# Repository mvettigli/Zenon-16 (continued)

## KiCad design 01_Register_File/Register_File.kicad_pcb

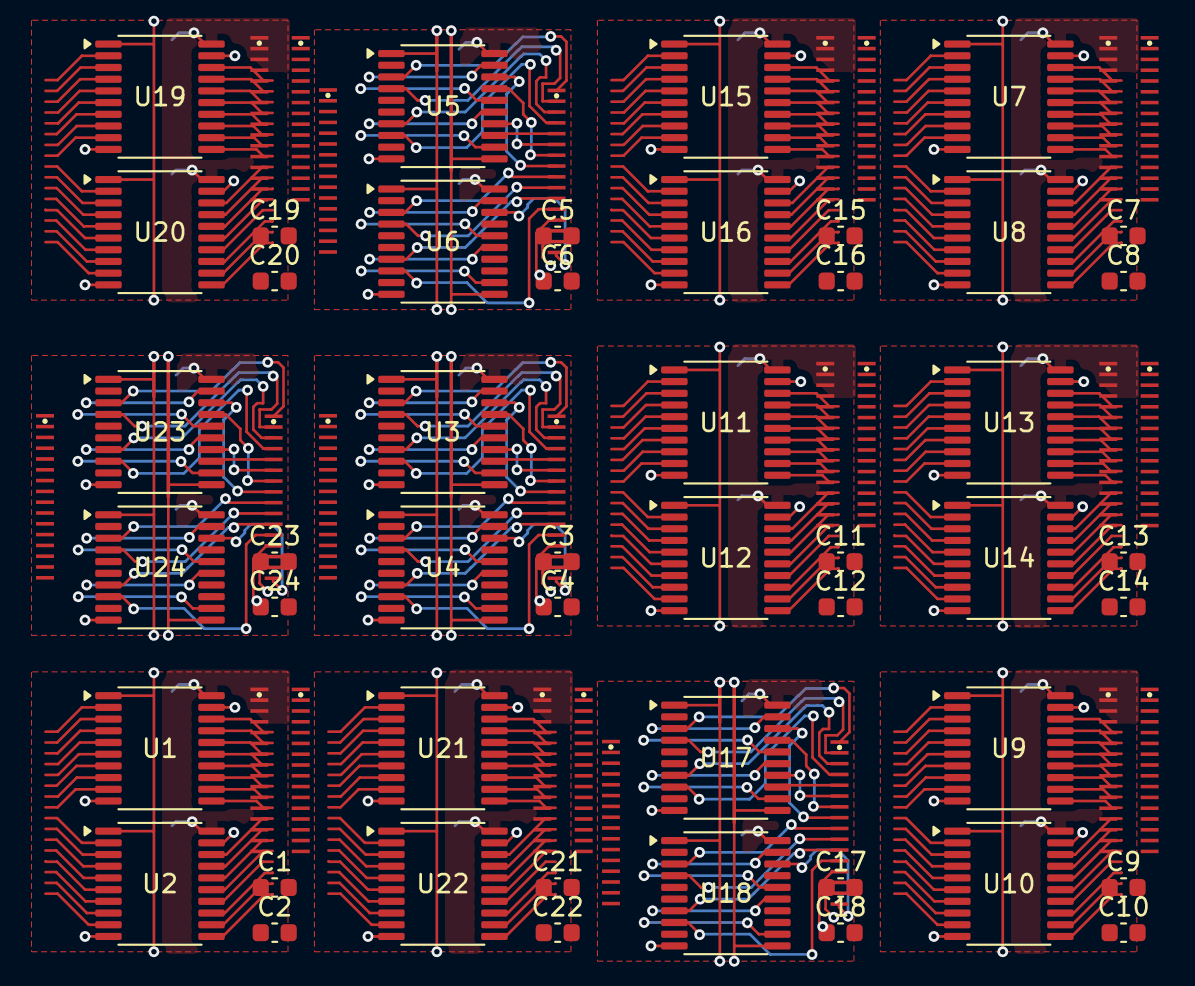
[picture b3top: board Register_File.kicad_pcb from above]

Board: 4 copper layers, 72 parts (0 on the bottom side), 95 nets.

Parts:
C1, C2, C3, C4, C5, C6, C7, C8, C9, C10, C11, C12, C13, C14, C15, C16, C17, C18, C19, C20, C21, C22, C23, C24: 100n; C_0603_1608Metric
J1, J7, J9, J11, J13, J15, J19, J21: In; Conn_01x16_p=0.6um
J2, J8, J10, J12, J14, J16, J20, J22: Out; Conn_01x16_p=0.6um
J3, J5, J17, J23: Data; Conn_01x16_p=0.6um
J4, J6, J18, J24: Content; Conn_01x16_p=0.6um
U1, U2, U7, U8, U9, U10, U11, U12, U13, U14, U15, U16, U19, U20, U21, U22: 74AHC541; TSSOP-20_4.4x6.5mm_P0.65mm
U3, U4, U5, U6, U17, U18, U23, U24: 74HC377; TSSOP-20_4.4x6.5mm_P0.65mm

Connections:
/A register Y-Bus1/~OE: U9.1 (G1), U10.1 (G1)
/A register Y-Bus2/~OE: U15.1 (G1), U16.1 (G1)
/A register Y-Bus3/~OE: U21.1 (G1), U22.1 (G1)
/A register Y-Bus/~OE: U1.1 (G1), U2.1 (G1)
/Ar0: J1.1, J4.1, J11.1, U1.2 (A0), U3.2 (Q0), U11.2 (A0)
/Ar1: J1.2, J4.2, J11.2, U1.3 (A1), U3.5 (Q1), U11.3 (A1)
/Ar2: J1.3, J4.3, J11.3, U1.4 (A2), U3.6 (Q2), U11.4 (A2)
/Ar3: J1.4, J4.4, J11.4, U1.5 (A3), U3.9 (Q3), U11.5 (A3)
/Ar4: J1.5, J4.5, J11.5, U1.6 (A4), U3.12 (Q4), U11.6 (A4)
/Ar5: J1.6, J4.6, J11.6, U1.7 (A5), U3.15 (Q5), U11.7 (A5)
/Ar6: J1.7, J4.7, J11.7, U1.8 (A6), U3.16 (Q6), U11.8 (A6)
/Ar7: J1.8, J4.8, J11.8, U1.9 (A7), U3.19 (Q7), U11.9 (A7)
/Ar8: J1.9, J4.9, J11.9, U2.2 (A0), U4.2 (Q0), U12.2 (A0)
/Ar9: J1.10, J4.10, J11.10, U2.3 (A1), U4.5 (Q1), U12.3 (A1)
/Ar10: J1.11, J4.11, J11.11, U2.4 (A2), U4.6 (Q2), U12.4 (A2)
/Ar11: J1.12, J4.12, J11.12, U2.5 (A3), U4.9 (Q3), U12.5 (A3)
/Ar12: J1.13, J4.13, J11.13, U2.6 (A4), U4.12 (Q4), U12.6 (A4)
/Ar13: J1.14, J4.14, J11.14, U2.7 (A5), U4.15 (Q5), U12.7 (A5)
/Ar14: J1.15, J4.15, J11.15, U2.8 (A6), U4.16 (Q6), U12.8 (A6)
/Ar15: J1.16, J4.16, J11.16, U2.9 (A7), U4.19 (Q7), U12.9 (A7)
/Br0: J6.1, J7.1, J9.1, J13.1, J15.1, J18.1, J19.1, J21.1, J24.1, U5.2 (Q0), U7.2 (A0), U9.2 (A0), U13.2 (A0), U15.2 (A0), U17.2 (Q0), U19.2 (A0), U21.2 (A0), U23.2 (Q0)
/Br1: J6.2, J7.2, J9.2, J13.2, J15.2, J18.2, J19.2, J21.2, J24.2, U5.5 (Q1), U7.3 (A1), U9.3 (A1), U13.3 (A1), U15.3 (A1), U17.5 (Q1), U19.3 (A1), U21.3 (A1), U23.5 (Q1)
/Br2: J6.3, J7.3, J9.3, J13.3, J15.3, J18.3, J19.3, J21.3, J24.3, U5.6 (Q2), U7.4 (A2), U9.4 (A2), U13.4 (A2), U15.4 (A2), U17.6 (Q2), U19.4 (A2), U21.4 (A2), U23.6 (Q2)
/Br3: J6.4, J7.4, J9.4, J13.4, J15.4, J18.4, J19.4, J21.4, J24.4, U5.9 (Q3), U7.5 (A3), U9.5 (A3), U13.5 (A3), U15.5 (A3), U17.9 (Q3), U19.5 (A3), U21.5 (A3), U23.9 (Q3)
/Br4: J6.5, J7.5, J9.5, J13.5, J15.5, J18.5, J19.5, J21.5, J24.5, U5.12 (Q4), U7.6 (A4), U9.6 (A4), U13.6 (A4), U15.6 (A4), U17.12 (Q4), U19.6 (A4), U21.6 (A4), U23.12 (Q4)
/Br5: J6.6, J7.6, J9.6, J13.6, J15.6, J18.6, J19.6, J21.6, J24.6, U5.15 (Q5), U7.7 (A5), U9.7 (A5), U13.7 (A5), U15.7 (A5), U17.15 (Q5), U19.7 (A5), U21.7 (A5), U23.15 (Q5)
/Br6: J6.7, J7.7, J9.7, J13.7, J15.7, J18.7, J19.7, J21.7, J24.7, U5.16 (Q6), U7.8 (A6), U9.8 (A6), U13.8 (A6), U15.8 (A6), U17.16 (Q6), U19.8 (A6), U21.8 (A6), U23.16 (Q6)
/Br7: J6.8, J7.8, J9.8, J13.8, J15.8, J18.8, J19.8, J21.8, J24.8, U5.19 (Q7), U7.9 (A7), U9.9 (A7), U13.9 (A7), U15.9 (A7), U17.19 (Q7), U19.9 (A7), U21.9 (A7), U23.19 (Q7)
/Br8: J6.9, J7.9, J9.9, J13.9, J15.9, J18.9, J19.9, J21.9, J24.9, U6.2 (Q0), U8.2 (A0), U10.2 (A0), U14.2 (A0), U16.2 (A0), U18.2 (Q0), U20.2 (A0), U22.2 (A0), U24.2 (Q0)
/Br9: J6.10, J7.10, J9.10, J13.10, J15.10, J18.10, J19.10, J21.10, J24.10, U6.5 (Q1), U8.3 (A1), U10.3 (A1), U14.3 (A1), U16.3 (A1), U18.5 (Q1), U20.3 (A1), U22.3 (A1), U24.5 (Q1)
/Br10: J6.11, J7.11, J9.11, J13.11, J15.11, J18.11, J19.11, J21.11, J24.11, U6.6 (Q2), U8.4 (A2), U10.4 (A2), U14.4 (A2), U16.4 (A2), U18.6 (Q2), U20.4 (A2), U22.4 (A2), U24.6 (Q2)
/Br11: J6.12, J7.12, J9.12, J13.12, J15.12, J18.12, J19.12, J21.12, J24.12, U6.9 (Q3), U8.5 (A3), U10.5 (A3), U14.5 (A3), U16.5 (A3), U18.9 (Q3), U20.5 (A3), U22.5 (A3), U24.9 (Q3)
/Br12: J6.13, J7.13, J9.13, J13.13, J15.13, J18.13, J19.13, J21.13, J24.13, U6.12 (Q4), U8.6 (A4), U10.6 (A4), U14.6 (A4), U16.6 (A4), U18.12 (Q4), U20.6 (A4), U22.6 (A4), U24.12 (Q4)
/Br13: J6.14, J7.14, J9.14, J13.14, J15.14, J18.14, J19.14, J21.14, J24.14, U6.15 (Q5), U8.7 (A5), U10.7 (A5), U14.7 (A5), U16.7 (A5), U18.15 (Q5), U20.7 (A5), U22.7 (A5), U24.15 (Q5)
/Br14: J6.15, J7.15, J9.15, J13.15, J15.15, J18.15, J19.15, J21.15, J24.15, U6.16 (Q6), U8.8 (A6), U10.8 (A6), U14.8 (A6), U16.8 (A6), U18.16 (Q6), U20.8 (A6), U22.8 (A6), U24.16 (Q6)
/Br15: J6.16, J7.16, J9.16, J13.16, J15.16, J18.16, J19.16, J21.16, J24.16, U6.19 (Q7), U8.9 (A7), U10.9 (A7), U14.9 (A7), U16.9 (A7), U18.19 (Q7), U20.9 (A7), U22.9 (A7), U24.19 (Q7)
/WBus0: J3.1, J5.1, J17.1, J23.1, U3.3 (D0), U5.3 (D0), U17.3 (D0), U23.3 (D0)
/WBus1: J3.2, J5.2, J17.2, J23.2, U3.4 (D1), U5.4 (D1), U17.4 (D1), U23.4 (D1)
/WBus2: J3.3, J5.3, J17.3, J23.3, U3.7 (D2), U5.7 (D2), U17.7 (D2), U23.7 (D2)
/WBus3: J3.4, J5.4, J17.4, J23.4, U3.8 (D3), U5.8 (D3), U17.8 (D3), U23.8 (D3)
/WBus4: J3.5, J5.5, J17.5, J23.5, U3.13 (D4), U5.13 (D4), U17.13 (D4), U23.13 (D4)
/WBus5: J3.6, J5.6, J17.6, J23.6, U3.14 (D5), U5.14 (D5), U17.14 (D5), U23.14 (D5)
/WBus6: J3.7, J5.7, J17.7, J23.7, U3.17 (D6), U5.17 (D6), U17.17 (D6), U23.17 (D6)
/WBus7: J3.8, J5.8, J17.8, J23.8, U3.18 (D7), U5.18 (D7), U17.18 (D7), U23.18 (D7)
/WBus8: J3.9, J5.9, J17.9, J23.9, U4.3 (D0), U6.3 (D0), U18.3 (D0), U24.3 (D0)
/WBus9: J3.10, J5.10, J17.10, J23.10, U4.4 (D1), U6.4 (D1), U18.4 (D1), U24.4 (D1)
/WBus10: J3.11, J5.11, J17.11, J23.11, U4.7 (D2), U6.7 (D2), U18.7 (D2), U24.7 (D2)
/WBus11: J3.12, J5.12, J17.12, J23.12, U4.8 (D3), U6.8 (D3), U18.8 (D3), U24.8 (D3)
/WBus12: J3.13, J5.13, J17.13, J23.13, U4.13 (D4), U6.13 (D4), U18.13 (D4), U24.13 (D4)
/WBus13: J3.14, J5.14, J17.14, J23.14, U4.14 (D5), U6.14 (D5), U18.14 (D5), U24.14 (D5)
/WBus14: J3.15, J5.15, J17.15, J23.15, U4.17 (D6), U6.17 (D6), U18.17 (D6), U24.17 (D6)
/WBus15: J3.16, J5.16, J17.16, J23.16, U4.18 (D7), U6.18 (D7), U18.18 (D7), U24.18 (D7)
/XBus0: J8.1, J12.1, J14.1, J20.1, U7.18 (Y0), U11.18 (Y0), U13.18 (Y0), U19.18 (Y0)
/XBus1: J8.2, J12.2, J14.2, J20.2, U7.17 (Y1), U11.17 (Y1), U13.17 (Y1), U19.17 (Y1)
/XBus2: J8.3, J12.3, J14.3, J20.3, U7.16 (Y2), U11.16 (Y2), U13.16 (Y2), U19.16 (Y2)
/XBus3: J8.4, J12.4, J14.4, J20.4, U7.15 (Y3), U11.15 (Y3), U13.15 (Y3), U19.15 (Y3)
/XBus4: J8.5, J12.5, J14.5, J20.5, U7.14 (Y4), U11.14 (Y4), U13.14 (Y4), U19.14 (Y4)
/XBus5: J8.6, J12.6, J14.6, J20.6, U7.13 (Y5), U11.13 (Y5), U13.13 (Y5), U19.13 (Y5)
/XBus6: J8.7, J12.7, J14.7, J20.7, U7.12 (Y6), U11.12 (Y6), U13.12 (Y6), U19.12 (Y6)
/XBus7: J8.8, J12.8, J14.8, J20.8, U7.11 (Y7), U11.11 (Y7), U13.11 (Y7), U19.11 (Y7)
/XBus8: J8.9, J12.9, J14.9, J20.9, U8.18 (Y0), U12.18 (Y0), U14.18 (Y0), U20.18 (Y0)
/XBus9: J8.10, J12.10, J14.10, J20.10, U8.17 (Y1), U12.17 (Y1), U14.17 (Y1), U20.17 (Y1)
/XBus10: J8.11, J12.11, J14.11, J20.11, U8.16 (Y2), U12.16 (Y2), U14.16 (Y2), U20.16 (Y2)
/XBus11: J8.12, J12.12, J14.12, J20.12, U8.15 (Y3), U12.15 (Y3), U14.15 (Y3), U20.15 (Y3)
/XBus12: J8.13, J12.13, J14.13, J20.13, U8.14 (Y4), U12.14 (Y4), U14.14 (Y4), U20.14 (Y4)
/XBus13: J8.14, J12.14, J14.14, J20.14, U8.13 (Y5), U12.13 (Y5), U14.13 (Y5), U20.13 (Y5)
/XBus14: J8.15, J12.15, J14.15, J20.15, U8.12 (Y6), U12.12 (Y6), U14.12 (Y6), U20.12 (Y6)
/XBus15: J8.16, J12.16, J14.16, J20.16, U8.11 (Y7), U12.11 (Y7), U14.11 (Y7), U20.11 (Y7)
/YBus0: J2.1, J10.1, J16.1, J22.1, U1.18 (Y0), U9.18 (Y0), U15.18 (Y0), U21.18 (Y0)
/YBus1: J2.2, J10.2, J16.2, J22.2, U1.17 (Y1), U9.17 (Y1), U15.17 (Y1), U21.17 (Y1)
/YBus2: J2.3, J10.3, J16.3, J22.3, U1.16 (Y2), U9.16 (Y2), U15.16 (Y2), U21.16 (Y2)
/YBus3: J2.4, J10.4, J16.4, J22.4, U1.15 (Y3), U9.15 (Y3), U15.15 (Y3), U21.15 (Y3)
/YBus4: J2.5, J10.5, J16.5, J22.5, U1.14 (Y4), U9.14 (Y4), U15.14 (Y4), U21.14 (Y4)
/YBus5: J2.6, J10.6, J16.6, J22.6, U1.13 (Y5), U9.13 (Y5), U15.13 (Y5), U21.13 (Y5)
/YBus6: J2.7, J10.7, J16.7, J22.7, U1.12 (Y6), U9.12 (Y6), U15.12 (Y6), U21.12 (Y6)
/YBus7: J2.8, J10.8, J16.8, J22.8, U1.11 (Y7), U9.11 (Y7), U15.11 (Y7), U21.11 (Y7)
/YBus8: J2.9, J10.9, J16.9, J22.9, U2.18 (Y0), U10.18 (Y0), U16.18 (Y0), U22.18 (Y0)
/YBus9: J2.10, J10.10, J16.10, J22.10, U2.17 (Y1), U10.17 (Y1), U16.17 (Y1), U22.17 (Y1)
/YBus10: J2.11, J10.11, J16.11, J22.11, U2.16 (Y2), U10.16 (Y2), U16.16 (Y2), U22.16 (Y2)
/YBus11: J2.12, J10.12, J16.12, J22.12, U2.15 (Y3), U10.15 (Y3), U16.15 (Y3), U22.15 (Y3)
/YBus12: J2.13, J10.13, J16.13, J22.13, U2.14 (Y4), U10.14 (Y4), U16.14 (Y4), U22.14 (Y4)
/YBus13: J2.14, J10.14, J16.14, J22.14, U2.13 (Y5), U10.13 (Y5), U16.13 (Y5), U22.13 (Y5)
/YBus14: J2.15, J10.15, J16.15, J22.15, U2.12 (Y6), U10.12 (Y6), U16.12 (Y6), U22.12 (Y6)
/YBus15: J2.16, J10.16, J16.16, J22.16, U2.11 (Y7), U10.11 (Y7), U16.11 (Y7), U22.11 (Y7)
CLK: U3.11 (CP), U4.11 (CP), U5.11 (CP), U6.11 (CP), U17.11 (CP), U18.11 (CP), U23.11 (CP), U24.11 (CP)
GND: C1.2, C2.2, C3.2, C4.2, C5.2, C6.2, C7.2, C8.2, C9.2, C10.2, C11.2, C12.2, C13.2, C14.2, C15.2, C16.2, C17.2, C18.2, C19.2, C20.2, C21.2, C22.2, C23.2, C24.2, U1.10 (GND), U1.19 (G2), U2.10 (GND), U2.19 (G2), U3.10 (GND), U4.10 (GND), U5.10 (GND), U6.10 (GND), U7.10 (GND), U7.19 (G2), U8.10 (GND), U8.19 (G2), U9.10 (GND), U9.19 (G2), U10.10 (GND), U10.19 (G2), U11.10 (GND), U11.19 (G2), U12.10 (GND), U12.19 (G2), U13.10 (GND), U13.19 (G2), U14.10 (GND), U14.19 (G2), U15.10 (GND), U15.19 (G2), U16.10 (GND), U16.19 (G2), U17.10 (GND), U18.10 (GND), U19.10 (GND), U19.19 (G2), U20.10 (GND), U20.19 (G2), U21.10 (GND), U21.19 (G2), U22.10 (GND), U22.19 (G2), U23.10 (GND), U24.10 (GND)
VCC: C1.1, C2.1, C3.1, C4.1, C5.1, C6.1, C7.1, C8.1, C9.1, C10.1, C11.1, C12.1, C13.1, C14.1, C15.1, C16.1, C17.1, C18.1, C19.1, C20.1, C21.1, C22.1, C23.1, C24.1, U1.20 (VCC), U2.20 (VCC), U3.20 (VCC), U4.20 (VCC), U5.20 (VCC), U6.20 (VCC), U7.20 (VCC), U8.20 (VCC), U9.20 (VCC), U10.20 (VCC), U11.20 (VCC), U12.20 (VCC), U13.20 (VCC), U14.20 (VCC), U15.20 (VCC), U16.20 (VCC), U17.20 (VCC), U18.20 (VCC), U19.20 (VCC), U20.20 (VCC), U21.20 (VCC), U22.20 (VCC), U23.20 (VCC), U24.20 (VCC)
~ArWE: U3.1 (~E), U4.1 (~E)
~ArXO: U11.1 (G1), U12.1 (G1)
~BrWE: U5.1 (~E), U6.1 (~E)
~BrXO: U7.1 (G1), U8.1 (G1)
~CrWE: U17.1 (~E), U18.1 (~E)
~CrXO: U13.1 (G1), U14.1 (G1)
~DrWE: U23.1 (~E), U24.1 (~E)
~DrXO: U19.1 (G1), U20.1 (G1)

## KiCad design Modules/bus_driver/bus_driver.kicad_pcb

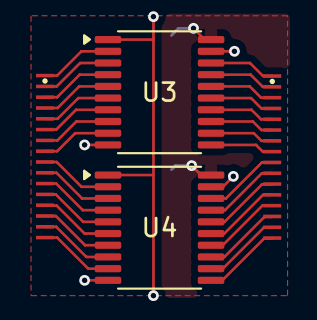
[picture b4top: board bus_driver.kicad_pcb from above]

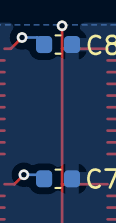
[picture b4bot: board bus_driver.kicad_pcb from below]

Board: 4 copper layers, 6 parts (2 on the bottom side), 35 nets.

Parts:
C7, C8: 100n; C_0603_1608Metric
J3: In; Conn_01x16_p=0.6um
J4: Out; Conn_01x16_p=0.6um
U3, U4: 74AHC541; TSSOP-20_4.4x6.5mm_P0.65mm

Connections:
/Q0: J3.1, U3.2 (A0)
/Q1: J3.2, U3.3 (A1)
/Q2: J3.3, U3.4 (A2)
/Q3: J3.4, U3.5 (A3)
/Q4: J3.5, U3.6 (A4)
/Q5: J3.6, U3.7 (A5)
/Q6: J3.7, U3.8 (A6)
/Q7: J3.8, U3.9 (A7)
/Q8: J3.9, U4.2 (A0)
/Q9: J3.10, U4.3 (A1)
/Q10: J3.11, U4.4 (A2)
/Q11: J3.12, U4.5 (A3)
/Q12: J3.13, U4.6 (A4)
/Q13: J3.14, U4.7 (A5)
/Q14: J3.15, U4.8 (A6)
/Q15: J3.16, U4.9 (A7)
/W0: J4.1, U3.18 (Y0)
/W1: J4.2, U3.17 (Y1)
/W2: J4.3, U3.16 (Y2)
/W3: J4.4, U3.15 (Y3)
/W4: J4.5, U3.14 (Y4)
/W5: J4.6, U3.13 (Y5)
/W6: J4.7, U3.12 (Y6)
/W7: J4.8, U3.11 (Y7)
/W8: J4.9, U4.18 (Y0)
/W9: J4.10, U4.17 (Y1)
/W10: J4.11, U4.16 (Y2)
/W11: J4.12, U4.15 (Y3)
/W12: J4.13, U4.14 (Y4)
/W13: J4.14, U4.13 (Y5)
/W14: J4.15, U4.12 (Y6)
/W15: J4.16, U4.11 (Y7)
/~OE: U3.1 (G1), U4.1 (G1)
GND: C7.2, C8.2, U3.10 (GND), U3.19 (G2), U4.10 (GND), U4.19 (G2)
VCC: C7.1, C8.1, U3.20 (VCC), U4.20 (VCC)

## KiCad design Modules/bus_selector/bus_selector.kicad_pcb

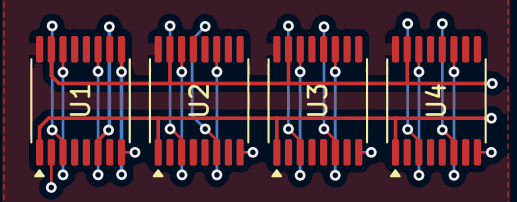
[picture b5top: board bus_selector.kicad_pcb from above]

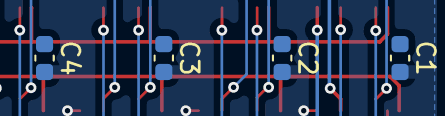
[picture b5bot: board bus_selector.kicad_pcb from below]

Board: 4 copper layers, 8 parts (4 on the bottom side), 4 nets.

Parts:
C1, C2, C3, C4: 100n; C_0603_1608Metric
U1, U2, U3, U4: 74HC157; TSSOP-16_4.4x5mm_P0.65mm

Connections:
/Sel: U1.1 (S), U2.1 (S), U3.1 (S), U4.1 (S)
/~EN: U1.15 (E), U2.15 (E), U3.15 (E), U4.15 (E)
GND: C1.2, C2.2, C3.2, C4.2, U1.8 (GND), U2.8 (GND), U3.8 (GND), U4.8 (GND)
VCC: C1.1, C2.1, C3.1, C4.1, U1.16 (VCC), U2.16 (VCC), U3.16 (VCC), U4.16 (VCC)

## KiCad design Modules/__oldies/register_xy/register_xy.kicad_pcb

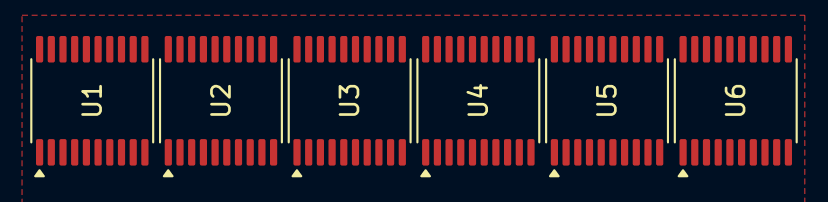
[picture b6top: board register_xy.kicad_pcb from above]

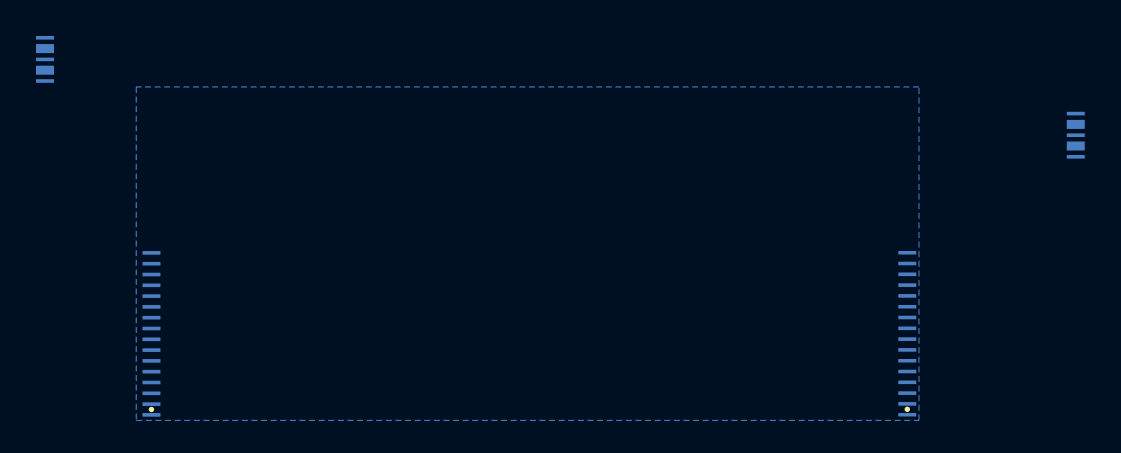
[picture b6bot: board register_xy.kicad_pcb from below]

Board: 2 copper layers, 10 parts (4 on the bottom side), 22 nets, no tracks yet.

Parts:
J1: SX; Conn_01x05_p=0.6um_PWR
J2: SX; Conn_01x16_p=0.6um
J3: DX; Conn_01x05_p=0.6um_PWR
J4: DX; Conn_01x16_p=0.6um
U1, U2: 74LS377; TSSOP-20_4.4x6.5mm_P0.65mm
U3, U4, U5, U6: 74AHC541; TSSOP-20_4.4x6.5mm_P0.65mm

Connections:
/1Q0: J2.1, J4.1, U1.2 (Q0), U3.2 (A0), U5.2 (A0)
/1Q1: J2.2, J4.2, U1.5 (Q1), U3.3 (A1), U5.3 (A1)
/1Q2: J2.3, J4.3, U1.6 (Q2), U3.4 (A2), U5.4 (A2)
/1Q3: J2.4, J4.4, U1.9 (Q3), U3.5 (A3), U5.5 (A3)
/1Q4: J2.5, J4.5, U1.12 (Q4), U3.6 (A4), U5.6 (A4)
/1Q5: J2.6, J4.6, U1.15 (Q5), U3.7 (A5), U5.7 (A5)
/1Q6: J2.7, J4.7, U1.16 (Q6), U3.8 (A6), U5.8 (A6)
/1Q7: J2.8, J4.8, U1.19 (Q7), U3.9 (A7), U5.9 (A7)
/2Q0: J2.9, J4.9, U2.2 (Q0), U4.2 (A0), U6.2 (A0)
/2Q1: J2.10, J4.10, U2.5 (Q1), U4.3 (A1), U6.3 (A1)
/2Q2: J2.11, J4.11, U2.6 (Q2), U4.4 (A2), U6.4 (A2)
/2Q3: J2.12, J4.12, U2.9 (Q3), U4.5 (A3), U6.5 (A3)
/2Q4: J2.13, J4.13, U2.12 (Q4), U4.6 (A4), U6.6 (A4)
/2Q5: J2.14, J4.14, U2.15 (Q5), U4.7 (A5), U6.7 (A5)
/2Q6: J2.15, J4.15, U2.16 (Q6), U4.8 (A6), U6.8 (A6)
/2Q7: J2.16, J4.16, U2.19 (Q7), U4.9 (A7), U6.9 (A7)
/CLK: J1.3, J3.3, U1.11 (CP), U2.11 (CP)
/~WE: U1.1 (~E), U2.1 (~E)
/~XE: J1.1, J3.1, U3.1 (G1), U4.1 (G1)
/~YE: J1.5, J3.5, U5.1 (G1), U6.1 (G1)
GND: J1.4, J3.4, U1.10 (GND), U2.10 (GND), U3.10 (GND), U3.19 (G2), U4.10 (GND), U4.19 (G2), U5.10 (GND), U5.19 (G2), U6.10 (GND), U6.19 (G2)
VCC: J1.2, J3.2, U1.20 (VCC), U2.20 (VCC), U3.20 (VCC), U4.20 (VCC), U5.20 (VCC), U6.20 (VCC)

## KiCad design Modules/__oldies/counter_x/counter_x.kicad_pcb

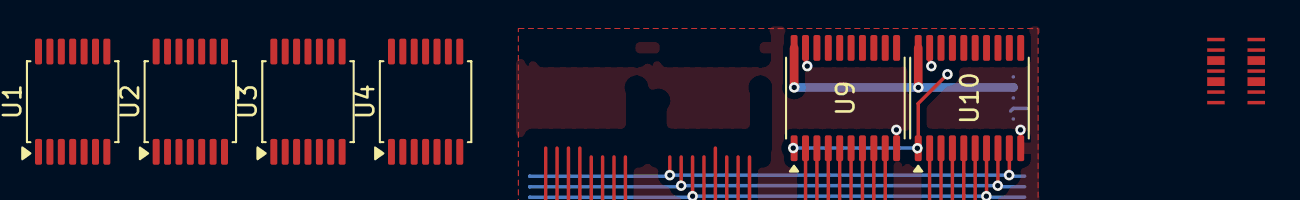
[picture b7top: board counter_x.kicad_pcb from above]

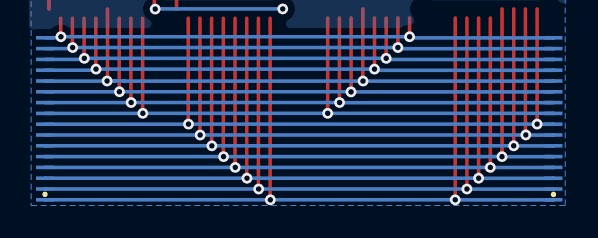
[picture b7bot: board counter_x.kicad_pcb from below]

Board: 2 copper layers, 10 parts (2 on the bottom side), 26 nets.

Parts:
J1: SX; Conn_01x07_p=0.6um_PWR
J2: DX; Conn_01x07_p=0.6um_PWR
J6: SX; Conn_01x16_p=0.6um
J8: DX; Conn_01x16_p=0.6um
U1, U2, U3, U4: 74HC191; TSSOP-14_4.4x5mm_P0.65mm
U9, U10: 74AHC541; TSSOP-20_4.4x6.5mm_P0.65mm

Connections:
/1Q0: J6.1, J8.1, U1.3 (Q0), U9.2 (A0)
/1Q1: J6.2, J8.2, U1.2 (Q1), U9.3 (A1)
/1Q2: J6.3, J8.3, U1.6 (Q2), U9.4 (A2)
/1Q3: J6.4, J8.4, U1.7 (Q3), U9.5 (A3)
/1Q4: J6.5, J8.5, U2.3 (Q0), U9.6 (A4)
/1Q5: J6.6, J8.6, U2.2 (Q1), U9.7 (A5)
/1Q6: J6.7, J8.7, U2.6 (Q2), U9.8 (A6)
/1Q7: J6.8, J8.8, U2.7 (Q3), U9.9 (A7)
/2Q0: J6.9, J8.9, U3.3 (Q0), U10.2 (A0)
/2Q1: J6.10, J8.10, U3.2 (Q1), U10.3 (A1)
/2Q2: J6.11, J8.11, U3.6 (Q2), U10.4 (A2)
/2Q3: J6.12, J8.12, U3.7 (Q3), U10.5 (A3)
/2Q4: J6.13, J8.13, U4.3 (Q0), U10.6 (A4)
/2Q5: J6.14, J8.14, U4.2 (Q1), U10.7 (A5)
/2Q6: J6.15, J8.15, U4.6 (Q2), U10.8 (A6)
/2Q7: J6.16, J8.16, U4.7 (Q3), U10.9 (A7)
/CLK: J1.4, J2.4, U1.14 (Cp), U2.14 (Cp), U3.14 (Cp), U4.14 (Cp)
/~CE: J1.7, J2.7, U1.4 (Ce)
/~PL: J1.1, J2.1, U1.11 (Pl), U2.11 (Pl), U3.11 (Pl), U4.11 (Pl)
/~U/D: J1.6, J2.6, U1.5 (D/U), U2.5 (D/U), U3.5 (D/U), U4.5 (D/U)
/~XE: J1.2, J2.2, U9.1 (G1), U10.1 (G1)
GND: J1.5, J2.5, U1.8 (GND), U2.8 (GND), U3.8 (GND), U4.8 (GND), U9.10 (GND), U9.19 (G2), U10.10 (GND), U10.19 (G2)
unnamed: U1.13 (Rc), U2.4 (Ce)
unnamed: U2.13 (Rc), U3.4 (Ce)
unnamed: U3.13 (Rc), U4.4 (Ce)
VCC: J1.3, J2.3, U9.20 (VCC), U10.20 (VCC)

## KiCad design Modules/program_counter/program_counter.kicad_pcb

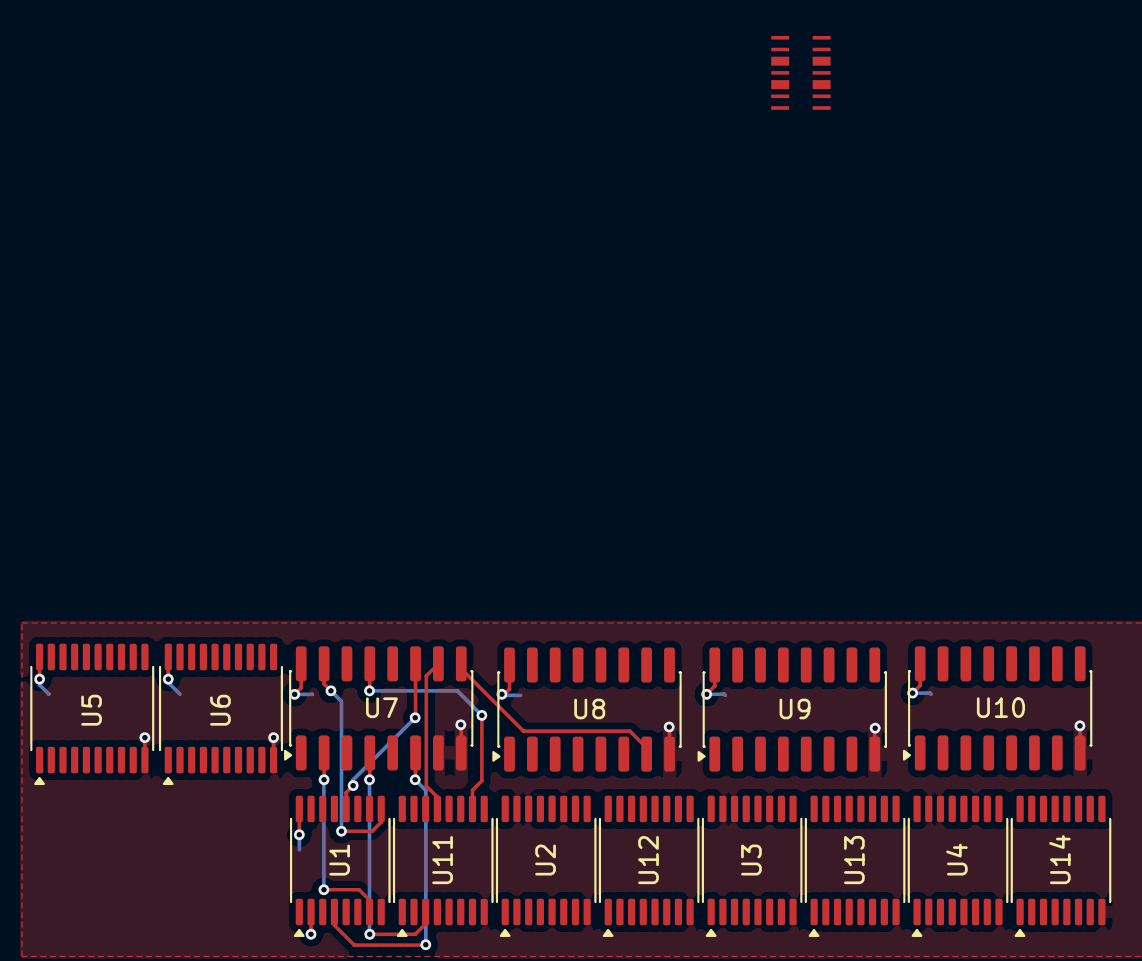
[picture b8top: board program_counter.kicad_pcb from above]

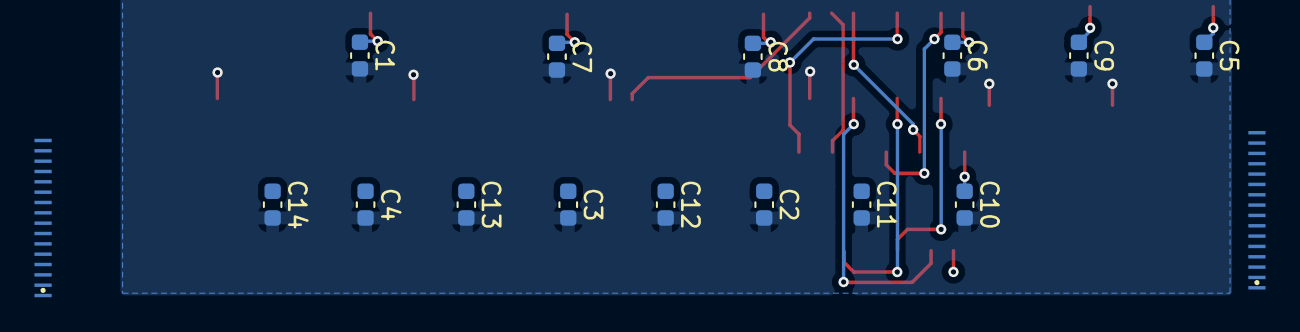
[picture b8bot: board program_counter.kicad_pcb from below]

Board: 4 copper layers, 32 parts (16 on the bottom side), 74 nets.

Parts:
C1, C2, C3, C4, C5, C6, C7, C8, C9, C10, C11, C12, C13, C14: 100n; C_0603_1608Metric
J1: SX; Conn_01x07_p=0.6um_PWR
J2: DX; Conn_01x07_p=0.6um_PWR
J3: SX; Conn_01x16_p=0.6um
J4: DX; Conn_01x16_p=0.6um
U1, U2, U3, U4, U11, U12, U13, U14: 74LS157; TSSOP-16_4.4x5mm_P0.65mm
U5, U6: 74HC377; TSSOP-20_4.4x6.5mm_P0.65mm
U7, U8, U9, U10: 74HC283; SOIC-16_3.9x9.9mm_P1.27mm

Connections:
/1B0: U1.4 (Za), U7.6 (B1)
/1B1: U1.7 (Zb), U7.2 (B2)
/1B2: U1.9 (Zc), U7.15 (B3)
/1B3: U1.12 (Zd), U7.11 (B4)
/1B4: U2.4 (Za), U8.6 (B1)
/1B5: U2.7 (Zb), U8.2 (B2)
/1B6: U2.9 (Zc), U8.15 (B3)
/1B7: U2.12 (Zd), U8.11 (B4)
/1D0: U5.3 (D0), U11.4 (Za)
/1D1: U5.4 (D1), U11.7 (Zb)
/1D2: U5.7 (D2), U11.9 (Zc)
/1D3: U5.8 (D3), U11.12 (Zd)
/1D4: U5.13 (D4), U12.4 (Za)
/1D5: U5.14 (D5), U12.7 (Zb)
/1D6: U5.17 (D6), U12.9 (Zc)
/1D7: U5.18 (D7), U12.12 (Zd)
/1P0: J3.1, J4.1, U5.2 (Q0), U7.5 (A1)
/1P1: J3.2, J4.2, U5.5 (Q1), U7.3 (A2)
/1P2: J3.3, J4.3, U5.6 (Q2), U7.14 (A3)
/1P3: J3.4, J4.4, U5.9 (Q3), U7.12 (A4)
/1P4: J3.5, J4.5, U5.12 (Q4), U8.5 (A1)
/1P5: J3.6, J4.6, U5.15 (Q5), U8.3 (A2)
/1P6: J3.7, J4.7, U5.16 (Q6), U8.14 (A3)
/1P7: J3.8, J4.8, U5.19 (Q7), U8.12 (A4)
/1S0: U7.4 (S1), U11.3 (I1a)
/1S1: U7.1 (S2), U11.6 (I1b)
/1S2: U7.13 (S3), U11.10 (I1c)
/1S3: U7.10 (S4), U11.13 (I1d)
/1S4: U8.4 (S1), U12.3 (I1a)
/1S5: U8.1 (S2), U12.6 (I1b)
/1S6: U8.13 (S3), U12.10 (I1c)
/1S7: U8.10 (S4), U12.13 (I1d)
/2B0: U3.4 (Za), U9.6 (B1)
/2B1: U3.7 (Zb), U9.2 (B2)
/2B2: U3.9 (Zc), U9.15 (B3)
/2B3: U3.12 (Zd), U9.11 (B4)
/2B4: U4.4 (Za), U10.6 (B1)
/2B5: U4.7 (Zb), U10.2 (B2)
/2B6: U4.9 (Zc), U10.15 (B3)
/2B7: U4.12 (Zd), U10.11 (B4)
/2D0: U6.3 (D0), U13.4 (Za)
/2D1: U6.4 (D1), U13.7 (Zb)
/2D2: U6.7 (D2), U13.9 (Zc)
/2D3: U6.8 (D3), U13.12 (Zd)
/2D4: U6.13 (D4), U14.4 (Za)
/2D5: U6.14 (D5), U14.7 (Zb)
/2D6: U6.17 (D6), U14.9 (Zc)
/2D7: U6.18 (D7), U14.12 (Zd)
/2P0: J3.9, J4.9, U6.2 (Q0), U9.5 (A1)
/2P1: J3.10, J4.10, U6.5 (Q1), U9.3 (A2)
/2P2: J3.11, J4.11, U6.6 (Q2), U9.14 (A3)
/2P3: J3.12, J4.12, U6.9 (Q3), U9.12 (A4)
/2P4: J3.13, J4.13, U6.12 (Q4), U10.5 (A1)
/2P5: J3.14, J4.14, U6.15 (Q5), U10.3 (A2)
/2P6: J3.15, J4.15, U6.16 (Q6), U10.14 (A3)
/2P7: J3.16, J4.16, U6.19 (Q7), U10.12 (A4)
/2S0: U9.4 (S1), U13.3 (I1a)
/2S1: U9.1 (S2), U13.6 (I1b)
/2S2: U9.13 (S3), U13.10 (I1c)
/2S3: U9.10 (S4), U13.13 (I1d)
/2S4: U10.4 (S1), U14.3 (I1a)
/2S5: U10.1 (S2), U14.6 (I1b)
/2S6: U10.13 (S3), U14.10 (I1c)
/2S7: U10.10 (S4), U14.13 (I1d)
/CLK: J1.4, J2.4, U5.11 (CP), U6.11 (CP)
/RST: J1.7, J2.7, U11.15 (E), U12.15 (E), U13.15 (E), U14.15 (E)
/~Abs: J1.6, J2.6, U11.1 (S), U12.1 (S), U13.1 (S), U14.1 (S)
/~CE: J1.2, J2.2, U1.1 (S), U2.1 (S), U3.1 (S), U4.1 (S)
/~EN: J1.1, J2.1, U5.1 (~E), U6.1 (~E)
GND: C1.2, C2.2, C3.2, C4.2, C5.2, C6.2, C7.2, C8.2, C9.2, C10.2, C11.2, C12.2, C13.2, C14.2, J1.5, J2.5, U1.5 (I0b), U1.8 (GND), U1.11 (I0c), U1.14 (I0d), U1.15 (E), U2.2 (I0a), U2.5 (I0b), U2.8 (GND), U2.11 (I0c), U2.14 (I0d), U2.15 (E), U3.2 (I0a), U3.5 (I0b), U3.8 (GND), U3.11 (I0c), U3.14 (I0d), U3.15 (E), U4.2 (I0a), U4.5 (I0b), U4.8 (GND), U4.11 (I0c), U4.14 (I0d), U4.15 (E), U5.10 (GND), U6.10 (GND), U7.7 (C0), U7.8 (GND), U8.8 (GND), U9.8 (GND), U10.8 (GND), U11.8 (GND), U12.8 (GND), U13.8 (GND), U14.8 (GND)
unnamed: U7.9 (C4), U8.7 (C0)
unnamed: U8.9 (C4), U9.7 (C0)
unnamed: U9.9 (C4), U10.7 (C0)
VCC: C1.1, C2.1, C3.1, C4.1, C5.1, C6.1, C7.1, C8.1, C9.1, C10.1, C11.1, C12.1, C13.1, C14.1, J1.3, J2.3, U1.2 (I0a), U1.16 (VCC), U2.16 (VCC), U3.16 (VCC), U4.16 (VCC), U5.20 (VCC), U6.20 (VCC), U7.16 (VCC), U8.16 (VCC), U9.16 (VCC), U10.16 (VCC), U11.16 (VCC), U12.16 (VCC), U13.16 (VCC), U14.16 (VCC)
